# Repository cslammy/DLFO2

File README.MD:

Digital LFO using AVR328 MCU and embedded C.  Please see this blog post for more information:
http://audiodiwhy.blogspot.com/2021/10/dirty-digital-lfo-done.html

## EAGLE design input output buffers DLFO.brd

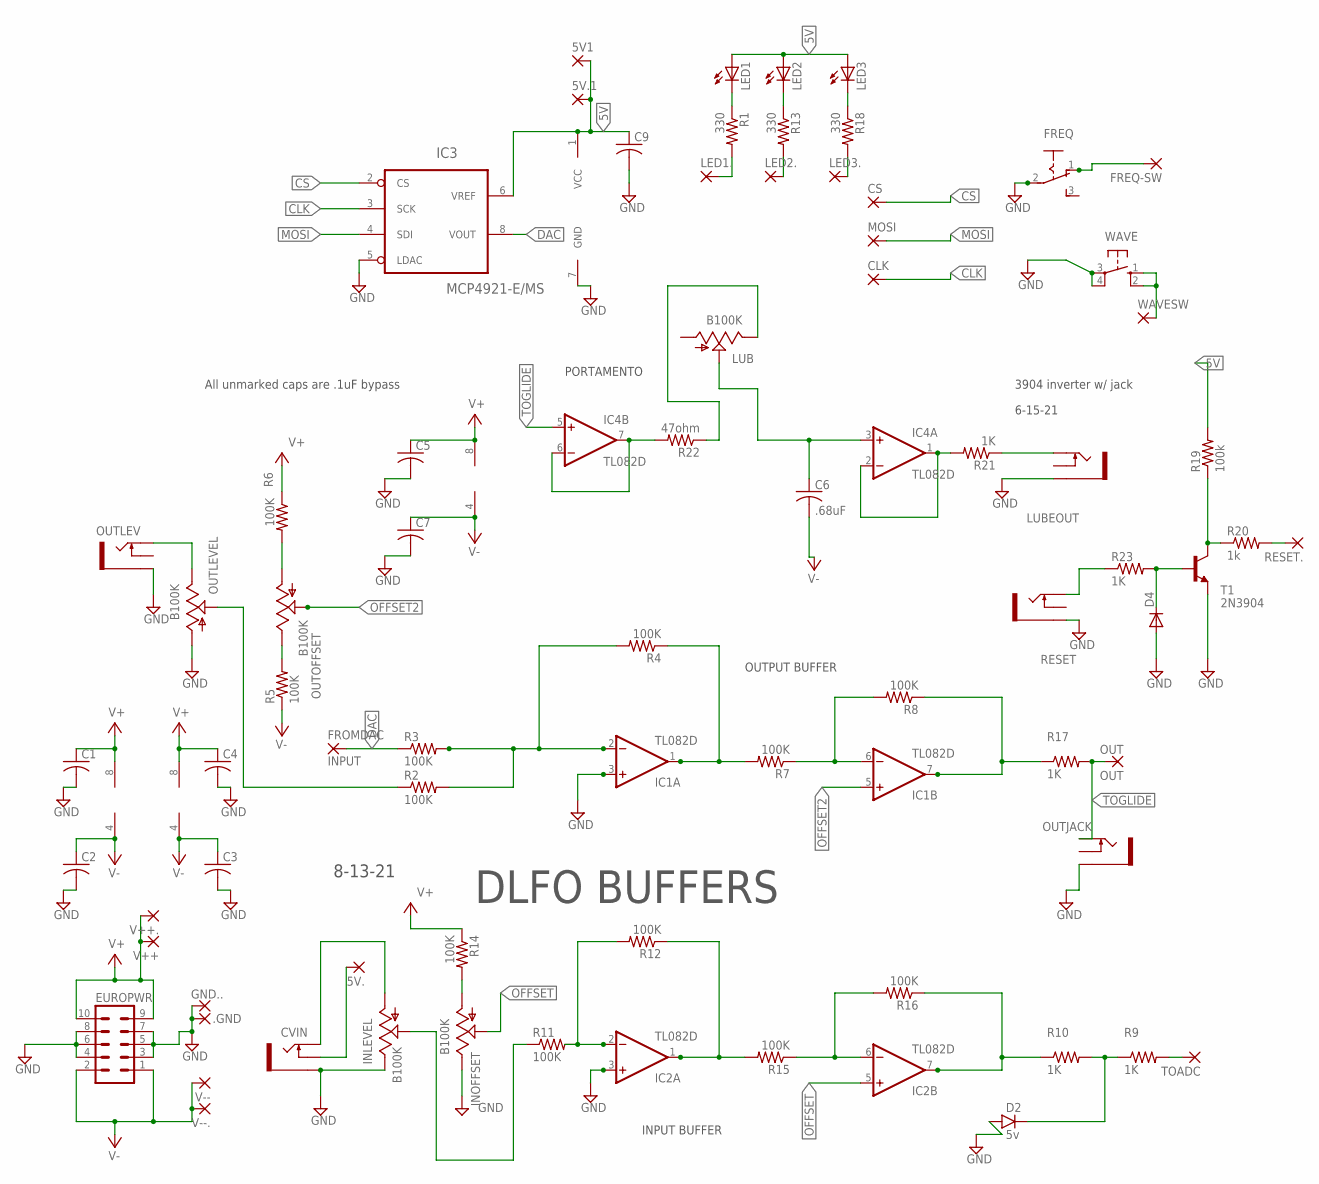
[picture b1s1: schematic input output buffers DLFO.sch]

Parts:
5V1, 5V.1: WIREPAD2,54/1,0; 2,54/1,0
5V., .GND: 3,17/1,3
C1, C2, C3, C4, C5, C7, C9: C-USC0603; C0603
C6: .68uF; C050-024X044
CLK: WIREPAD2,54/1,1; 2,54/1,1
CS: WIREPAD2,54/1,0; 2,54/1,0
CVIN: THONKICONNNEW; WQP-PJ301M-12_JACK
D2: 5v; DO41-2
D4: 1N4148DO35-10; DO35-10
EUROPWR: EURO_POWER_HEADERREGULAR; EURO_POWER_HEADER
FREQ: M251
FREQ-SW: WIREPAD2,54/0,9; 2,54/0,9
FROMDAC: INPUT; 3,17/1,3
GND..: 3,17/1,3
IC1, IC2, IC4: TL082D; SO08
IC3: MCP4921-E/MS; MSOP-8
INLEVEL: B100K; 9MM_SNAP-IN_POT
INOFFSET: B100K; 9MM_SNAP-IN_POT
LED1, LED2, LED3: LED3MM
LED1., LED2.: WIREPAD2,54/1,0; 2,54/1,0
LED3.: WIREPAD2,54/1,1; 2,54/1,1
LUB: B100K; 9MM_SNAP-IN_POT
LUBEOUT: THONKICONNNEW; WQP-PJ301M-12_JACK
MOSI: WIREPAD2,54/1,0; 2,54/1,0
OUT: OUT; 3,17/1,3
OUTJACK: THONKICONNNEW; WQP-PJ301M-12_JACK
OUTLEV: THONKICONNNEW; WQP-PJ301M-12_JACK
OUTLEVEL: B100K; 9MM_SNAP-IN_POT
OUTOFFSET: B100K; 9MM_SNAP-IN_POT
R1, R13, R18: 330; R0603
R2, R3, R4, R5, R6, R7, R8, R11, R12, R14, R15, R16: 100K; R0603
R9, R10, R17, R21, R23: 1K; R0603
R19: 100k; R0603
R20: 1k; R0603
R22: 47ohm; R0603
RESET: THONKICONNNEW; WQP-PJ301M-12_JACK
RESET.: 3,17/1,3
T1: 2N3904; TO92
TOADC: 3,17/1,3
V++, V++.: 3,17/1,3
V--, V--.: 3,17/1,3
WAVE: 10-XX; B3F-10XX
WAVESW: WIREPAD2,54/0,9; 2,54/0,9

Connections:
5V: 5V1.1, 5V.1.1, C9.1, IC3.1 (VCC), IC3.6 (VREF), LED1.A, LED2.A, LED3.A, R19.2
CLK: CLK.1, IC3.3 (SCK)
CS: CS.1, IC3.2 (CS)
DAC: FROMDAC.1, IC3.8 (VOUT), R3.1
GND: .GND.1, C1.2, C2.2, C3.2, C4.2, C5.2, C7.2, C9.2, CVIN.P$3_SLEEVE (SLEEVE), D2.A, D4.A, EUROPWR.3, EUROPWR.4, EUROPWR.5, EUROPWR.6, EUROPWR.7, EUROPWR.8, FREQ.2, GND...1, IC1.3 (+IN), IC2.3 (+IN), IC3.5 (LDAC), IC3.7 (GND), INLEVEL.3 (E), INOFFSET.3 (E), LUBEOUT.P$3_SLEEVE (SLEEVE), OUTJACK.P$3_SLEEVE (SLEEVE), OUTLEV.P$3_SLEEVE (SLEEVE), OUTLEVEL.1 (A), RESET.P$3_SLEEVE (SLEEVE), T1.3 (E), WAVE.3, WAVE.4 (P1)
LED1: LED1..1, R1.2
LED2: LED2..1, R13.2
MOSI: IC3.4 (SDI), MOSI.1
unnamed: OUTLEV.P$1_TIP (TIP), OUTLEVEL.3 (E)
unnamed: IC1.6 (-IN), R7.1, R8.2
unnamed: IC1.1 (OUT), R4.1, R7.2
unnamed: INOFFSET.1 (A), R14.2
unnamed: D2.C, R9.1, R10.2
unnamed: IC2.2 (-IN), R11.2, R12.2
unnamed: OUTLEVEL.2 (S), R2.1
unnamed: OUTOFFSET.1 (A), R6.2
unnamed: OUTOFFSET.3 (E), R5.2
unnamed: IC2.1 (OUT), R12.1, R15.2
unnamed: IC1.7 (OUT), R8.1, R17.1
unnamed: R23.1, RESET.P$1_TIP (TIP)
unnamed: CVIN.P$1_TIP (TIP), INLEVEL.1 (A)
unnamed: D4.C, R23.2, T1.2 (B)
unnamed: IC2.6 (-IN), R15.1, R16.2
unnamed: IC2.7 (OUT), R10.1, R16.1
unnamed: IC1.2 (-IN), R2.2, R3.2, R4.2
unnamed: LED3..1, R18.2
unnamed: R9.2, TOADC.1
unnamed: INLEVEL.2 (S), R11.1
unnamed: LED1.K (C), R1.1
unnamed: WAVE.1 (S), WAVE.2 (S1), WAVESW.1
unnamed: LED2.K (C), R13.1
unnamed: FREQ.1 (O), FREQ-SW.1
unnamed: LED3.K (C), R18.1
unnamed: R19.1, R20.1, T1.1 (C)
unnamed: 5V..1, CVIN.P$2_SWITCH (SWITCH)
unnamed: IC4.6 (-IN), IC4.7 (OUT), R22.2
unnamed: IC4.1 (OUT), IC4.2 (-IN), R21.2
unnamed: LUBEOUT.P$1_TIP (TIP), R21.1
unnamed: LUB.3 (E), R22.1
unnamed: C6.1, IC4.3 (+IN), LUB.2 (S)
unnamed: R20.2, RESET..1
OFFSET: IC2.5 (+IN), INOFFSET.2 (S)
OFFSET2: IC1.5 (+IN), OUTOFFSET.2 (S)
TOGLIDE: IC4.5 (+IN), OUT.1, OUTJACK.P$1_TIP (TIP), R17.2
V+: C1.1, C4.1, C5.1, EUROPWR.9, EUROPWR.10, IC1.8 (V+), IC2.8 (V+), IC4.8 (V+), R6.1, R14.1, V++.1, V++..1
V-: C2.1, C3.1, C6.2, C7.1, EUROPWR.1, EUROPWR.2, IC1.4 (V-), IC2.4 (V-), IC4.4 (V-), R5.1, V--.1, V--..1

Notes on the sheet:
OUTPUT BUFFER
INPUT BUFFER
DLFO BUFFERS
8-13-21
PORTAMENTO
3904 inverter w/ jack
6-15-21
All unmarked caps are .1uF bypass

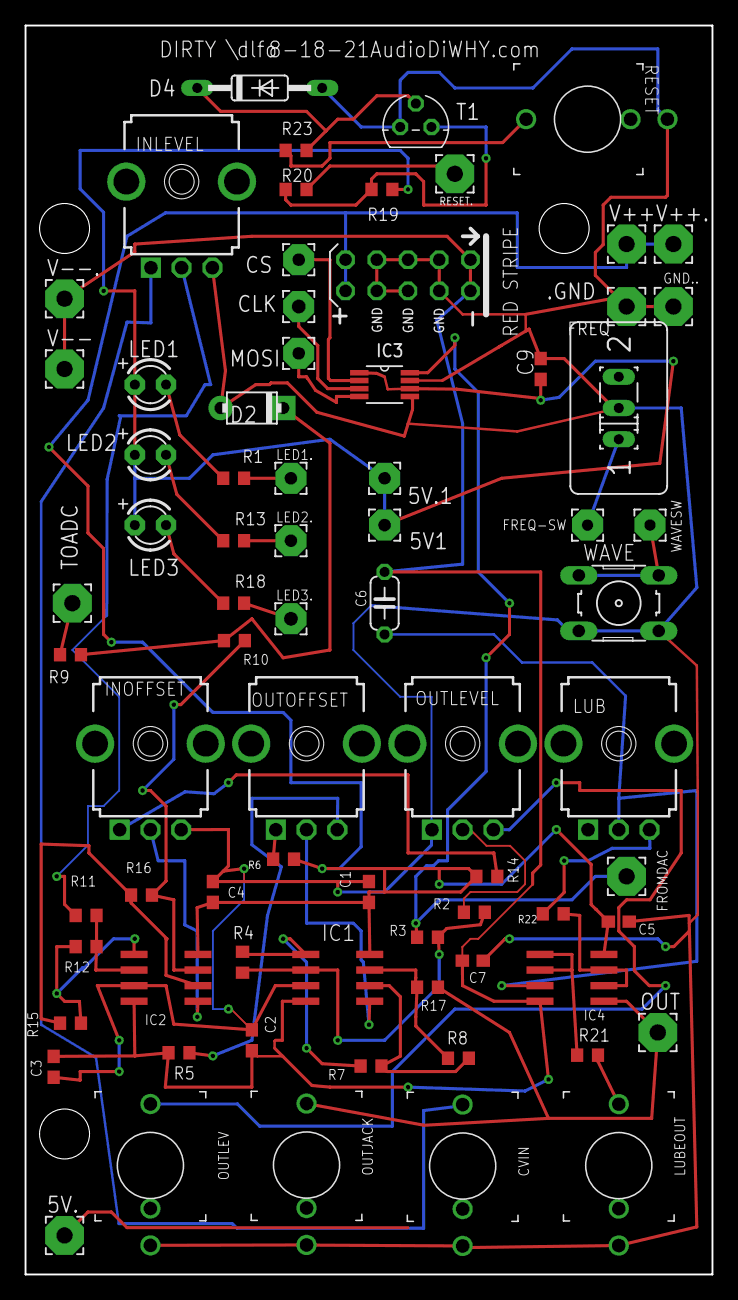
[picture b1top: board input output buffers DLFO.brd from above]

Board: 2 copper layers, 55.9 x 101.6 mm, 75 parts (0 on the bottom side), 46 nets.

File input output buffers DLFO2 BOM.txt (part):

Partlist exported from C:/Users/clamm/Dropbox/eagle/DLFO/8-17-21/input output DLFO buffer PCB/input output buffers DLFO.sch at 10/31/2021 9:24 AM

Part      Value        Device                   Package            Description                                       DATA_SHEET                                                             MF MPN      OC_FARNELL OC_NEWARK POPULARITY SPICEPREFIX
                                                                                                                           4                     
C1                     C-USC0603                C0603              CAPACITOR, American symbol                                                                                                                                37         C          
C2                     C-USC0603                C0603              CAPACITOR, American symbol                                                                                                                                37         C          
C3                     C-USC0603                C0603              CAPACITOR, American symbol                                                                                                                                37         C          
C4                     C-USC0603                C0603              CAPACITOR, American symbol                                                                                                                                37         C          
C5                     C-USC0603                C0603              CAPACITOR, American symbol                                                                                                                                37         C          
C6        .68uF        C-US050-024X044          C050-024X044       CAPACITOR, American symbol                                                                                                                                14         C          
C7                     C-USC0603                C0603              CAPACITOR, American symbol                                                                                                                                37         C          
C9                     C-USC0603                C0603              CAPACITOR, American symbol                                                                                                                                37         C          
CS                     WIREPAD2,54/1,0          2,54/1,0           Wire PAD connect wire on PCB                                                                                                                              4                     
CVIN                   THONKICONNNEW            WQP-PJ301M-12_JACK 3.5mm socket for Eurorack modular synths                                                                                                                                        
D2        5v           DO41.2                   DO41-2             DO-41 Package                                                                                                                                                                   
D4                     1N4148DO35-10            DO35-10            DIODE                                                                                                                                                                           
EUROPWR                EURO_POWER_HEADERREGULAR EURO_POWER_HEADER  Power Header                                                                                                                                                                    
FREQ                   M251                     M251               SLIDING SWITCH                                                                                                                                            1                     
IC1       TL082D       TL082D                   SO08               OP AMP                                            <a href="http://www.ti.com/lit/ds/symlink/tl084a.pdf"> Data sheet </a>                                                        
IC2       TL082D       TL082D                   SO08               OP AMP                                            <a href="http://www.ti.com/lit/ds/symlink/tl084a.pdf"> Data sheet </a>                                                        
IC3       MCP4921-E/MS MCP4921-E/MS             MSOP-8             Digital-to-Analog Converter                                                                                                                                                     
IC4       TL082D       TL082D                   SO08               OP AMP                                            <a href="http://www.ti.com/lit/ds/symlink/tl084a.pdf"> Data sheet </a>                                  1                     
INLEVEL   B100K        9MM_SNAP-IN_POT_         9MM_SNAP-IN_POT    9mm vertical snap-in pot, Alpha / Panasonic style                                                                                                                               
INOFFSET  B100K        9MM_SNAP-IN_POT_         9MM_SNAP-IN_POT    9mm vertical snap-in pot, Alpha / Panasonic style                                                                                                                               
LED1                   LED3MM                   LED3MM             LED                                                                                                                                                                             
                                                                                                                             4                     
LED2                   LED3MM                   LED3MM             LED                                                                                                                                                                             
                                                                                                                           4                     
LED3                   LED3MM                   LED3MM             LED                                                                                                                                                                             
                                                                                                                            2                     
LUB       B100K        9MM_SNAP-IN_POT_         9MM_SNAP-IN_POT    9mm vertical snap-in pot, Alpha / Panasonic style                                                                                                                               
LUBEOUT                THONKICONNNEW            WQP-PJ301M-12_JACK 3.5mm socket for Eurorack modular synths                                                                                                                                        
OUTJACK                THONKICONNNEW            WQP-PJ301M-12_JACK 3.5mm socket for Eurorack modular synths                                                                                                                                        
OUTLEV                 THONKICONNNEW            WQP-PJ301M-12_JACK 3.5mm socket for Eurorack modular synths                                                                                                                                        
OUTLEVEL  B100K        9MM_SNAP-IN_POT_         9MM_SNAP-IN_POT    9mm vertical snap-in pot, Alpha / Panasonic style                                                                                                                               
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
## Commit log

2021-10-31 Initial upload
    Details etc please see this post: http://audiodiwhy.blogspot.com/2021/10/dirty-digital-lfo-done.html
    You will also need the minimalist AVR board, repository is here. https://github.com/cslammy/AVR328-minimal
2021-11-03 Changed a comment
    No changes to actual code....
